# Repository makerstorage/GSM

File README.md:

**GSM Gate Opener**

For more details, check out the blog pages at

http://blog.makerstorage.com

MakerStorage invests time and resources providing this open source design, please support MakerStorage and open-source hardware by purchasing products from MakerStorage!

Designed by MakerStorage LLC.

Creative Commons Attribution, Share-Alike license, check https://creativecommons.org/licenses/by-sa/3.0/ for more information All text above must be included in any redistribution

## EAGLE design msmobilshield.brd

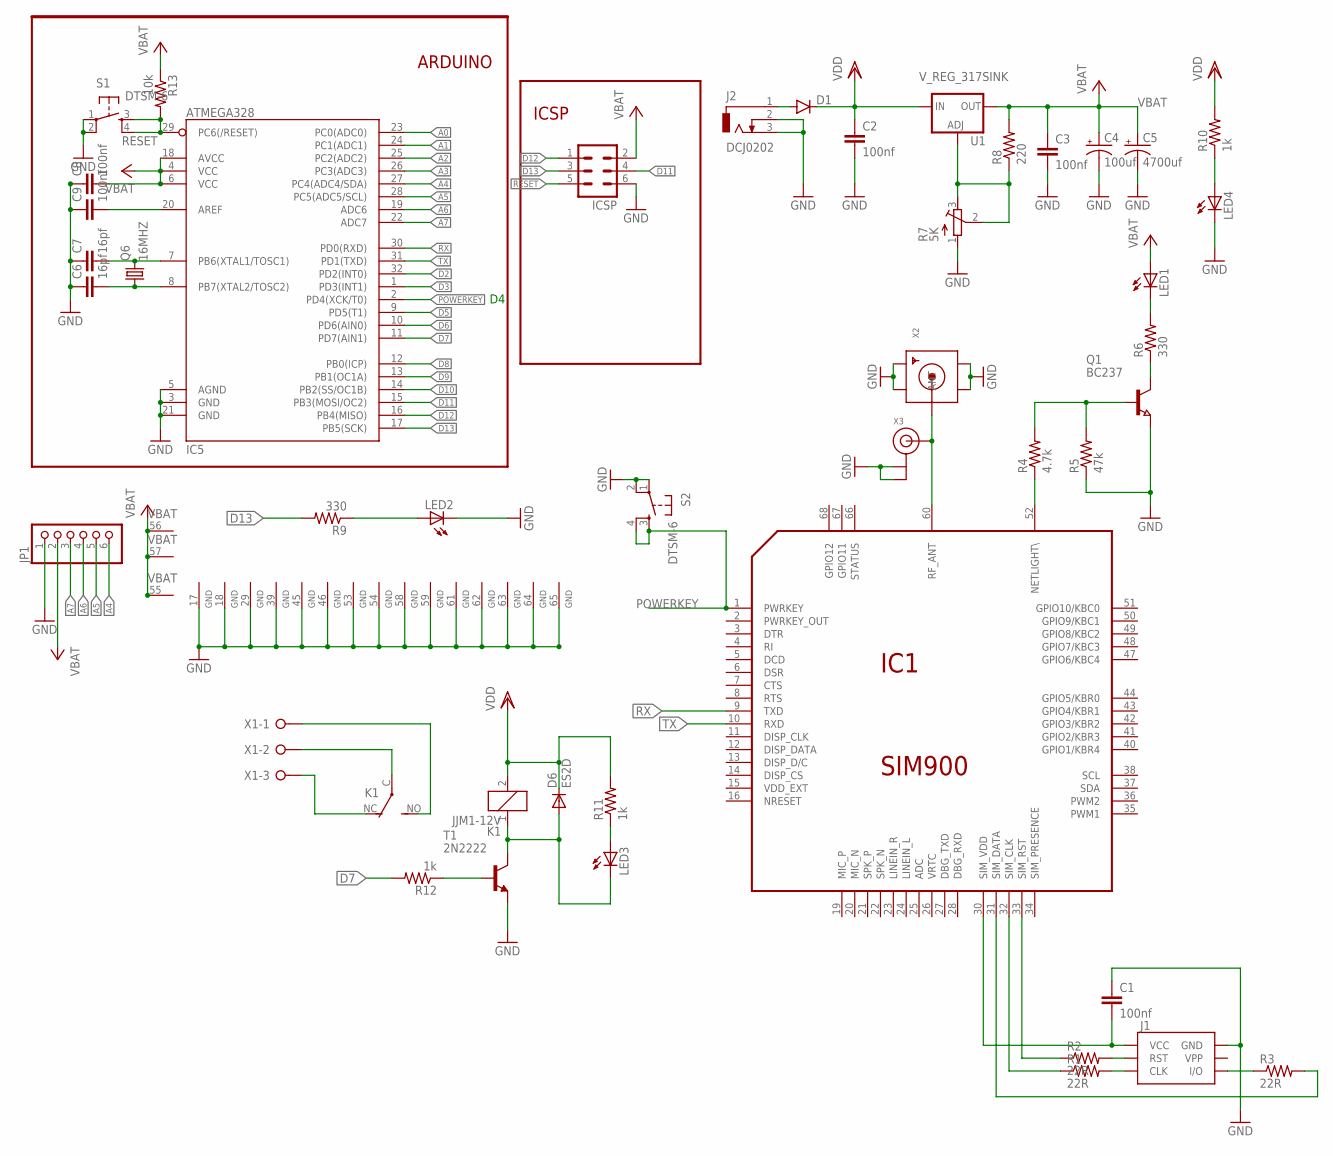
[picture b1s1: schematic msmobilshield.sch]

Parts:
C1, C2, C3, C8, C9: 100nf; C0805
C4: 100uf; CPOL-RADIAL-100UF-25V
C5: 4700uf; CPOL-RADIAL-1000UF-25V
C6, C7: 16pf; C0805
D1: DIODESMA; SMA-DIODE
D6: ES2D; SMB
IC1: SIM900
IC5: ATMEGA328; TQFP32-08
ICSP: ML6
J1: SIMHOLDERSIM; SIMHOLDER
J2: DCJ0202
JP1: PINHD-1X6; 1X06
K1: JJM1-12V; JJM1C
LED1, LED2, LED3, LED4: LEDCHIPLED_0805; CHIPLED_0805
Q1: BC237; SOT23
Q6: 16MHZ; HC49/S
R1, R2, R3: 22R; R0805
R4: 4.7k; R0805
R5: 47k; R0805
R6, R9: 330; R0805
R7: 5K; RTRIM3103
R8: 220; R0805
R10, R11, R12: 1k; R0805
R13: 10k; R0805
S1, S2: DTSM-6
T1: 2N2222; SOT23-BEC
U1: V_REG_317SINK; TO220-ADJ
X1: W237-3E
X2: SMACONNECTOR; SMA90_DIP
X3: ANTENNA_U.FL; U.FL

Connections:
A0: IC5.23 (PC0(ADC0))
A1: IC5.24 (PC1(ADC1))
A2: IC5.25 (PC2(ADC2))
A3: IC5.26 (PC3(ADC3))
A4: IC5.27 (PC4(ADC4/SDA)), JP1.6
A5: IC5.28 (PC5(ADC5/SCL)), JP1.5
A6: IC5.19 (ADC6), JP1.4
A7: IC5.22 (ADC7), JP1.3
D2: IC5.32 (PD2(INT0))
D3: IC5.1 (PD3(INT1))
D5: IC5.9 (PD5(T1))
D6: IC5.10 (PD6(AIN0))
D7: IC5.11 (PD7(AIN1)), R12.2
D8: IC5.12 (PB0(ICP))
D9: IC5.13 (PB1(OC1A))
D10: IC5.14 (PB2(SS/OC1B))
D11: IC5.15 (PB3(MOSI/OC2)), ICSP.4
D12: IC5.16 (PB4(MISO)), ICSP.1
D13: IC5.17 (PB5(SCK)), ICSP.3, R9.2
GND: C1.1, C2.2, C3.2, C4.2 (-), C5.-, C6.1, C7.1, C8.1, C9.1, IC1.17 (GND), IC1.18 (GND), IC1.29 (GND), IC1.39 (GND), IC1.45 (GND), IC1.46 (GND), IC1.53 (GND), IC1.54 (GND), IC1.58 (GND), IC1.59 (GND), IC1.61 (GND), IC1.62 (GND), IC1.63 (GND), IC1.64 (GND), IC1.65 (GND), IC5.3 (GND), IC5.5 (AGND), IC5.21 (GND), ICSP.6, J1.C5 (GND), J2.2, J2.3, JP1.1, LED2.C, LED4.C, Q1.2 (E), R5.1, R7.1 (A), S1.1, S1.2, S2.1, S2.2, T1.E, X2.GND1, X2.GND2, X2.GND3, X2.GND4, X3.1 (GND), X3.2 (GND)
unnamed: J1.C2 (RST), R2.2
unnamed: J1.C3 (CLK), R1.2
unnamed: J1.C7 (I/O), R3.1
unnamed: IC1.33 (SIM_RST), R2.1
unnamed: IC1.32 (SIM_CLK), R1.1
unnamed: IC1.31 (SIM_DATA), R3.2
unnamed: C1.2, IC1.30 (SIM_VDD), J1.C1 (VCC)
unnamed: IC1.60 (RF_ANT), X2.ANTENNA (ANT), X3.3 (SIGNAL)
unnamed: IC1.52 (NETLIGHT\), R4.1
unnamed: Q1.1 (B), R4.2, R5.2
unnamed: K1.C, X1.2
unnamed: Q1.3 (C), R6.1
unnamed: LED1.C, R6.2
unnamed: K1.NC (O), X1.3
unnamed: D1.A, J2.1
unnamed: K1.NO (S), X1.1
unnamed: R7.2 (S), R7.3 (E), R8.1, U1.ADJ
unnamed: LED2.A, R9.1
unnamed: LED4.A, R10.1
unnamed: C7.2, IC5.7 (PB6(XTAL1/TOSC1)), Q6.2
unnamed: C6.2, IC5.8 (PB7(XTAL2/TOSC2)), Q6.1
unnamed: C9.2, IC5.20 (AREF)
unnamed: R12.1, T1.B
unnamed: D6.A, K1.1, LED3.C, T1.C
unnamed: LED3.A, R11.1
POWERKEY: IC1.1 (PWRKEY), IC5.2 (PD4(XCK/T0)), S2.3, S2.4
RESET: IC5.29 (PC6(/RESET)), ICSP.5, R13.2, S1.3, S1.4
RX: IC1.9 (TXD), IC5.30 (PD0(RXD))
TX: IC1.10 (RXD), IC5.31 (PD1(TXD))
VBAT: C3.1, C4.1 (+), C5.+, C8.2, IC1.55 (VBAT), IC1.56 (VBAT), IC1.57 (VBAT), IC5.4 (VCC), IC5.6 (VCC), IC5.18 (AVCC), ICSP.2, JP1.2, LED1.A, R8.2, R13.1, U1.OUT
VDD: C2.1, D1.C, D6.C, K1.2, R10.2, R11.2, U1.IN

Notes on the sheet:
ICSP
ARDUINO

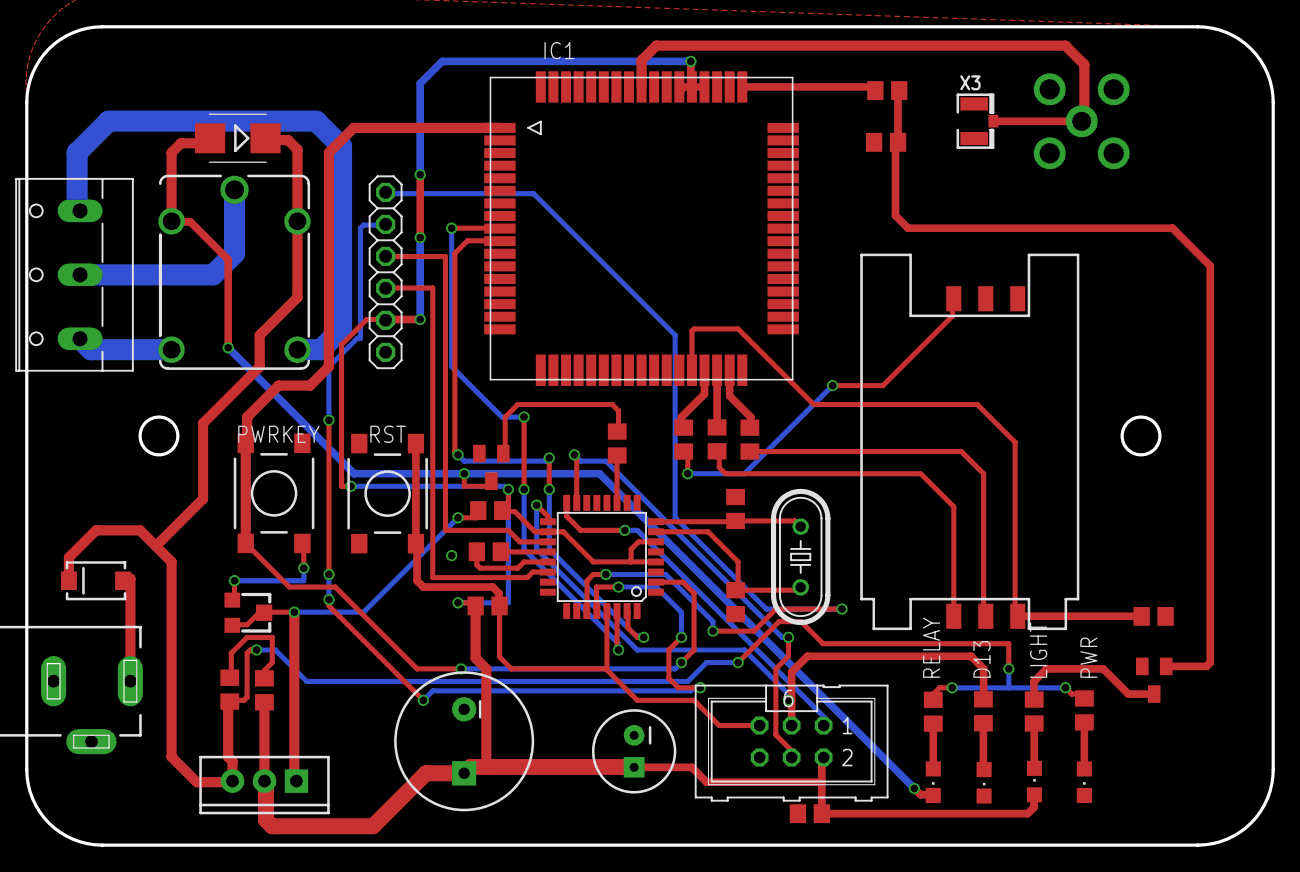
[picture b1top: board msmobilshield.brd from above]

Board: 2 copper layers, 99.0 x 65.0 mm, 44 parts (0 on the bottom side), 40 nets.

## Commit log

2016-12-03 boards and firmware
2016-12-03 small read me
2016-12-03 web app
2016-12-03 database

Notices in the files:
parts and their libraries:
SparkFun-Capacitors: Licensing: Creative Commons ShareAlike 4.0 International - https://creativecommons.org/licenses/by-sa/4.0
